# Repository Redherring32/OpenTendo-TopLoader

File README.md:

# OpenTendo-TopLoader
An Open Source HardWare (OSHW) recreation of the 1993 toploading NES motherboard (Also known as NES-101)

## Note on RGB and HDMI:

Neither RGB nor HDMI video output were or are a goal of the OpenTendo project, the goal was/is documentation and preservation, and the project was an exercise in reverse engineering. As such "improved" video outputs will not be added to OpenTendo-Toploader.

NESRGB and Hi-Def NES can be installed as normal, but will not be incorporated into the OpenTendo-Toploader PCB

## Repository Structure:

* Board Files: Contains all files necessary to open the project in KiCad, as well as the schematic and schematic symbols

* Component Footprints: Contains a library of all the custom footprints used on the board

The files required to order PCBs can be found under releases.

## Recommended PCB specs:

* 2 layers

* 106.1mmx155mm

* 1.6mm thickness

* HASL or ENiG surface finish

* And any color you want!

Image credit: 1UpRestorations

The design is 1:1 with the OEM board, everything is exactly as it was on the OEM board with hopefully no exceptions, this project does not include "improvements"

Since this project is open-source you may do as you like with it, whether that is to make boards for personal use, sell replacement NES boards, or to use the provided info for further custom PCB work/designs.

*Note:* At this point in time, any and all motherboards will require the use of an original CPU[1],  and PPU[2] to function.
  
These are the only two chips that are custom and have no direct replacement, the rest can be replaced with modern, and or easily available parts.

*[1]There is an aftermarket CPU, the part number is UA6527 (NTSC) or UA6527P (PAL), however they are known to have different sounding audio due to swapped duty cycles, as such they aren't a 100% identical substitute, they otherwise work though.

*[2]There is an aftermarket PPU that can be used; the part number is UA6528 (NTSC) or UA6538 (PAL), and it is available on Aliexpress.
While it works as a drop-in replacement, it isn't known whether it is compatible with all NES games.

Please read the release page for notes on any parts that must be harvested, or otherwise obtained separately from the BOM.

## License:

Licensed under
the TAPR Open Hardware License (www.tapr.org/OHL)

©Redherring32 2022-2023

## Credits

* 1UpRestorations, RetroSho, and OGHUGO: "Beta" testing

* ShankMods, and Retrocution: donating motherboards for reverse engineering

And to all of the awesome people in the NES scene, I wouldn't have been able to do this without the awesome work that some very clever people did before I got here.

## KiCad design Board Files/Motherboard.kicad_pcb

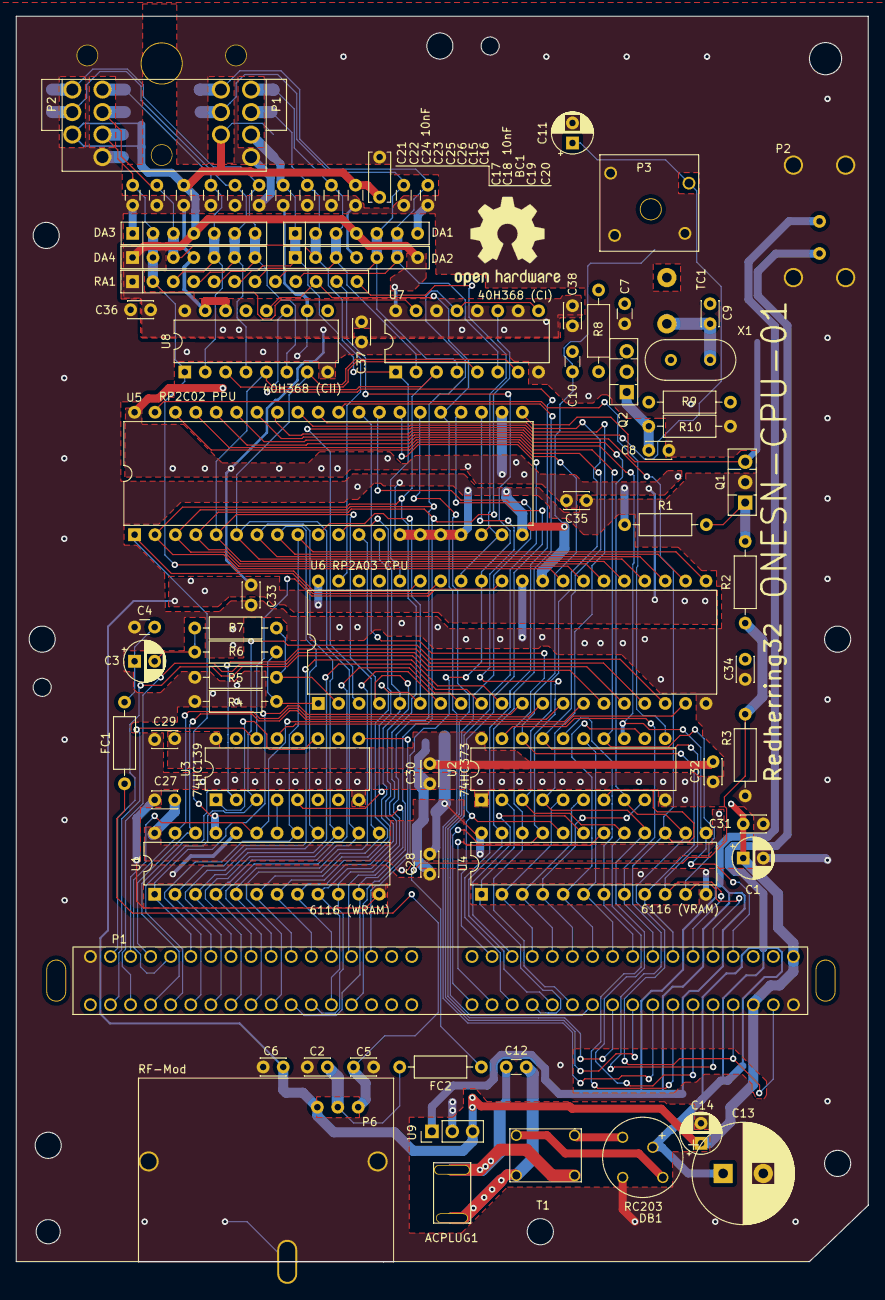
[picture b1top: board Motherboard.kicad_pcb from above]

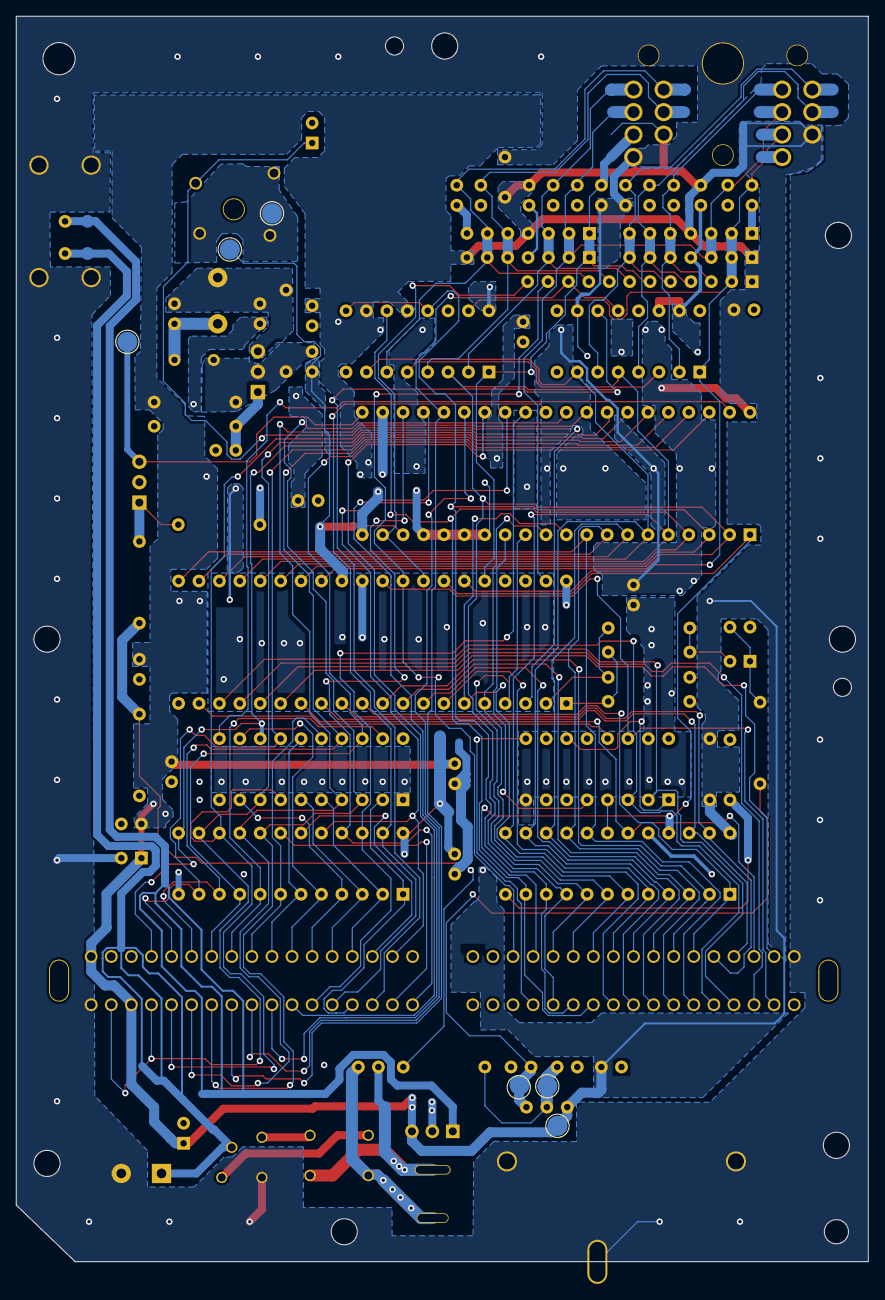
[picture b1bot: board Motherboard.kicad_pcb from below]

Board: 2 copper layers, 106.1 x 155.0 mm, 83 parts (6 on the bottom side), 92 nets.

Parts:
 : TestPoint_Pad_D2.5mm
 #2,  #3,  #4,  #5,  #6: TestPoint_Pad_D2.5mm
ACPLUG1: AC-JACK
BC1: 10nF; C_Disc_D6.0mm_W2.5mm_P5.00mm
C1: 100uF; CP_Radial_D5.0mm_P2.50mm
C2: 330pF; C_Disc_D3.0mm_W2.0mm_P2.50mm
C3, C14: 1uF; CP_Radial_D5.0mm_P2.50mm
C4: 220pF; C_Disc_D3.0mm_W1.6mm_P2.50mm
C5, C6, C8, C27, C28, C29, C30, C31, C32, C33, C34, C35, C36, C37, C38: 10nF; C_Disc_D3.0mm_W2.0mm_P2.50mm
C7, C15, C16, C17, C19, C20, C21, C22, C23, C25, C26: 330pF; C_Disc_D3.0mm_W1.6mm_P2.50mm
C9: 10pF; C_Disc_D3.0mm_W2.0mm_P2.50mm
C10, C12, C18, C24: 10nF; C_Disc_D3.0mm_W1.6mm_P2.50mm
C11: 0.47uF; CP_Radial_D5.0mm_P2.50mm
C13: 1500uF; CP_Radial_D12.5mm_P5.00mm
DA1, DA3: DAN601; R_Array_SIP7
DA2, DA4: UPA64H; R_Array_SIP7
DB1: RC203; Rectifier
FC1: 39u; R_Axial_DIN0207_L6.3mm_D2.5mm_P10.16mm_Horizontal
FC2: Ferrite_Coil; R_Axial_DIN0207_L6.3mm_D2.5mm_P10.16mm_Horizontal
P1: 72-Pin Connector; Cart Connector
P2: PowerSw; PowerSwitchV2
P3: ResetSw; ResetSwitchV2
P4: Controller_Port; Controller Ports
P6: RF-Mod; RF-MOD
Q1: 2SA937; TO-126-3_Vertical
Q2: 2SC2021; TO-126-3_Vertical
R1: 510; R_Axial_DIN0207_L6.3mm_D2.5mm_P10.16mm_Horizontal
R2: 430; R_Axial_DIN0207_L6.3mm_D2.5mm_P10.16mm_Horizontal
R3, R10: 150; R_Axial_DIN0207_L6.3mm_D2.5mm_P10.16mm_Horizontal
R4, R5: 160; R_Axial_DIN0207_L6.3mm_D2.5mm_P10.16mm_Horizontal
R6: 200; R_Axial_DIN0207_L6.3mm_D2.5mm_P10.16mm_Horizontal
R7: 100; R_Axial_DIN0207_L6.3mm_D2.5mm_P10.16mm_Horizontal
R8: 150K; R_Axial_DIN0207_L6.3mm_D2.5mm_P10.16mm_Horizontal
R9: 1.2K; R_Axial_DIN0207_L6.3mm_D2.5mm_P10.16mm_Horizontal
RA1: 12 x 10K; R_Array_SIP12
T1: 08RB01; Inductor
TC1: 30pF; TrimmerCap-THT
U1: 6116 (WRAM); DIP-24_W7.62mm
U2: 74HC373; DIP-20_W7.62mm
U3: 74HC139; DIP-16_W7.62mm
U4: 6116 (VRAM); DIP-24_W7.62mm
U5: RP2C02 PPU; DIP-40_W15.24mm
U6: RP2A03 CPU; DIP-40_W15.24mm
U7: 40H368 (CI); DIP-16_W7.62mm
U8: 40H368 (CII); DIP-16_W7.62mm
U9: L7805; PinHeader_1x03_P2.54mm_Vertical
X1: 21.47727 MHz; Crystal_HC49-U_Vertical

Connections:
/4016-D0: C17.1, DA1.3, DA2.3, P4.4-1, RA1.7, U7.2
/4016-D3: C19.1, DA1.5, DA2.5, P4.6-1, RA1.8, U7.4
/4016-D4: C20.1, DA1.6, DA2.6, P4.7-1, RA1.9, U7.6
/4017-D0: C23.1, DA3.5, DA4.5, P4.4-2, RA1.3, U8.2
/4017-D3: C25.1, DA3.6, DA4.6, P4.6-2, RA1.4, U8.4
/4017-D4: C26.1, DA3.7, DA4.7, P4.7-2, RA1.5, U8.6
/ALE: U2.11, U5.39
/AUDIO: #4.1, C5.1, FC1.1, P6.3
/CPU-A0: P1.13, U1.8, U5.12, U6.4
/CPU-A1: P1.12, U1.7, U5.11, U6.5
/CPU-A2: P1.11, U1.6, U5.10, U6.6
/CPU-A3: P1.10, U1.5, U6.7
/CPU-A4: P1.9, U1.4, U6.8
/CPU-A5: P1.8, U1.3, U6.9
/CPU-A6: P1.7, U1.2, U6.10
/CPU-A7: P1.6, U1.1, U6.11
/CPU-A8: P1.5, U1.23, U6.12
/CPU-A9: P1.4, U1.22, U6.13
/CPU-A10: P1.3, U1.19, U6.14
/CPU-A11: P1.2, U6.15
/CPU-A12: P1.39, U6.16
/CPU-A13: P1.40, U3.2, U6.17
/CPU-A14: P1.41, U3.3, U6.18
/CPU-A15: U3.13, U6.19
/CPU-D0: P1.49, U1.9, U5.2, U6.28, U7.3, U8.3
/CPU-D1: P1.48, U1.10, U5.3, U6.27, U7.9, U7.13
/CPU-D2: P1.47, U1.11, U5.4, U6.26, U7.11
/CPU-D3: P1.46, U1.13, U5.5, U6.25, U7.5, U8.5
/CPU-D4: P1.45, U1.14, U5.6, U6.24, U7.7, U8.7
/CPU-D5: P1.44, U1.15, U5.7, U6.23
/CPU-D6: P1.43, U1.16, U5.8, U6.22
/CPU-D7: P1.42, U1.17, U5.9, U6.21
/CPU-R~W: P1.14, U1.21, U5.1, U6.34
/GND: #2.1, BC1.1, C1.2, C2.1, C4.1, C5.2, C6.1, C7.1, C8.2, C11.2, C13.2, C14.2, C15.2, C16.2, C17.2, C18.2, C19.2, C20.2, C21.2, C22.2, C23.2, C24.2, C25.2, C26.2, C27.1, C28.1, C29.1, C30.1, C31.1, C32.1, C33.1, C34.1, C35.1, C36.1, C37.1, C38.1, DA1.7, DA2.4, DA3.1, DA4.4, DB1.2, P1.1, P1.72, P2.3, P3.2, P4.1-1, P4.1-2, P4.3, P4.4, P4.5, P6.4, Q1.2, R3.1, R4.1, R5.1, R10.2, U1.12, U1.20, U2.1, U2.10, U3.8, U3.15, U4.12, U5.14, U5.15, U5.16, U5.17, U5.20, U6.20, U6.30, U7.8, U8.8, U8.10, U8.14, U8.15, U9.2
/M2: P1.38, U3.14, U6.31
/OUT-0: C16.1, C22.1, DA1.2, DA2.2, DA3.3, DA4.3, P4.3-1, P4.3-2, U6.39
/PPU-A0: P1.29, U2.19, U4.8
/PPU-A1: P1.28, U2.16, U4.7
/PPU-A2: P1.27, U2.15, U4.6
/PPU-A3: P1.26, U2.12, U4.5
/PPU-A4: P1.25, U2.9, U4.4
/PPU-A5: P1.24, U2.6, U4.3
/PPU-A6: P1.23, U2.5, U4.2
/PPU-A7: P1.59, U2.2, U4.1
/PPU-A8: P1.60, U4.23, U5.30
/PPU-A9: P1.61, U4.22, U5.29
/PPU-A10: P1.63, U5.28
/PPU-A11: P1.62, U5.27
/PPU-A12: P1.64, U5.26
/PPU-A13: P1.65, RA1.10, U5.25, U8.12
/PPU-D0: P1.30, U2.18, U4.9, U5.38
/PPU-D1: P1.31, U2.17, U4.10, U5.37
/PPU-D2: P1.32, U2.14, U4.11, U5.36
/PPU-D3: P1.33, U2.13, U4.13, U5.35
/PPU-D4: P1.69, P1.71, U2.8, U4.14, U5.34
/PPU-D5: P1.68, U2.7, U4.15, U5.33
/PPU-D6: P1.67, U2.4, U4.16, U5.32
/PPU-D7: P1.66, U2.3, U4.17, U5.31
/PPU-~A13: P1.58, U8.11
/PPU-~CE: U3.5, U5.13
/PPU-~RD: P1.21, U4.20, U5.24
/PPU-~WE: P1.56, U4.21, U5.23
/SOUND-1: R4.2, R6.2, U6.1
/SOUND-2: R5.2, R7.2, U6.2
/SYS-CLK: .1, C10.1, U5.18, U6.29
/VCC: #6.1, BC1.2, C1.1, C6.2, C14.1, C18.1, C24.1, C27.2, C28.2, C29.2, C30.2, C31.2, C32.2, C33.2, C34.2, C35.2, C36.2, C37.2, C38.2, DA1.4, DA2.7, DA3.4, DA4.1, P1.36, P1.70, P4.5-1, P4.5-2, P6.1, R1.1, R9.2, RA1.1, U1.24, U2.20, U3.16, U4.24, U5.22, U5.40, U6.40, U7.10, U7.12, U7.14, U7.16, U8.16, U9.3
/VIDEO: #5.1, C2.2, FC2.2, P6.2
/VRAM-A10: P1.22, U4.19
/VRAM-~CE: P1.57, U4.18
/WRAM-~CE: U1.18, U3.4
/~IRQ: P1.15, RA1.11, U6.32
/~NMI: RA1.12, U5.19, U6.33
/~OE1: C15.1, DA1.1, DA2.1, P4.2-1, RA1.6, U6.36, U7.1
/~OE2: C21.1, DA3.2, DA4.2, P4.2-2, RA1.2, U6.35, U7.15, U8.1
/~ROMSEL: P1.50, U3.9
/~RST: C11.1, P3.1, U6.3
unnamed: ACPLUG1.1, C12.2, T1.1
unnamed: ACPLUG1.2, C12.1, T1.3
unnamed: C3.1, C4.2, FC1.2
unnamed: C3.2, R6.1, R7.1
unnamed: C7.2, C9.2, Q2.3, R8.2, TC1.2
unnamed: C8.1, Q2.1, R10.1
unnamed: C9.1, TC1.1, X1.2
unnamed: C10.2, Q2.2, R8.1, R9.1, X1.1
unnamed: C13.1, DB1.1, P2.1
unnamed: DB1.3, T1.4
unnamed: DB1.4, T1.2
unnamed: FC2.1, R2.1, R3.2
unnamed: P2.2, U9.1
unnamed: Q1.1, R1.2, R2.2
unnamed: #3.1, Q1.3, U5.21
unnamed: U3.1, U3.11

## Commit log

2020-09-26 +Various schematic reference and net label fixes
2020-10-31 + Started board outline + Finished up the schematic (hopefully) + Started creation of custom footprints
2021-06-04 + Completed schematic + Added RF Modulator schematic symbol + Added RF Modulator footprint + Added Reset Switch footprint + Completed Power Switch footprint + Continued board layout
2021-06-11 + Added screw holes to PCB + Added holes to Cartridge and Controller footprints
2021-06-19 + Finished component layout + Tidied silkscreen
2023-01-12 Almost done
    + Added zone cutouts to make copper pours more like OEM shape
    + Edited schematic to be more readable
    TO-DO:
    * Finish cutouts
    * Verify mounting, alignment, and connector hole placement and sizing.
2023-01-14 + Fixed hole sizing and placement issues + Updated Cartridge connector, Controller Port, PowerSwitch, and ResetSwitch footprints to fix pad placement issues + Fixed overlapping reference labeling in 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
2023-02-10 Add readme draft
2023-02-10 + Implemented fixes for issues found in testing
2023-02-17 Fix Issue #1
2026-01-31 + Migrate to Kicad 9 + Fix symbol issues caused by Kicad 6+ library and symbol name changes + Change "HEX BUFFERS" label to "CONTROLLER HEX BUFFERS" to match OpenTendo + Migrate legacy symbol .lib to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
2026-01-31 Update README.md
    Fix PAL PPU PN
